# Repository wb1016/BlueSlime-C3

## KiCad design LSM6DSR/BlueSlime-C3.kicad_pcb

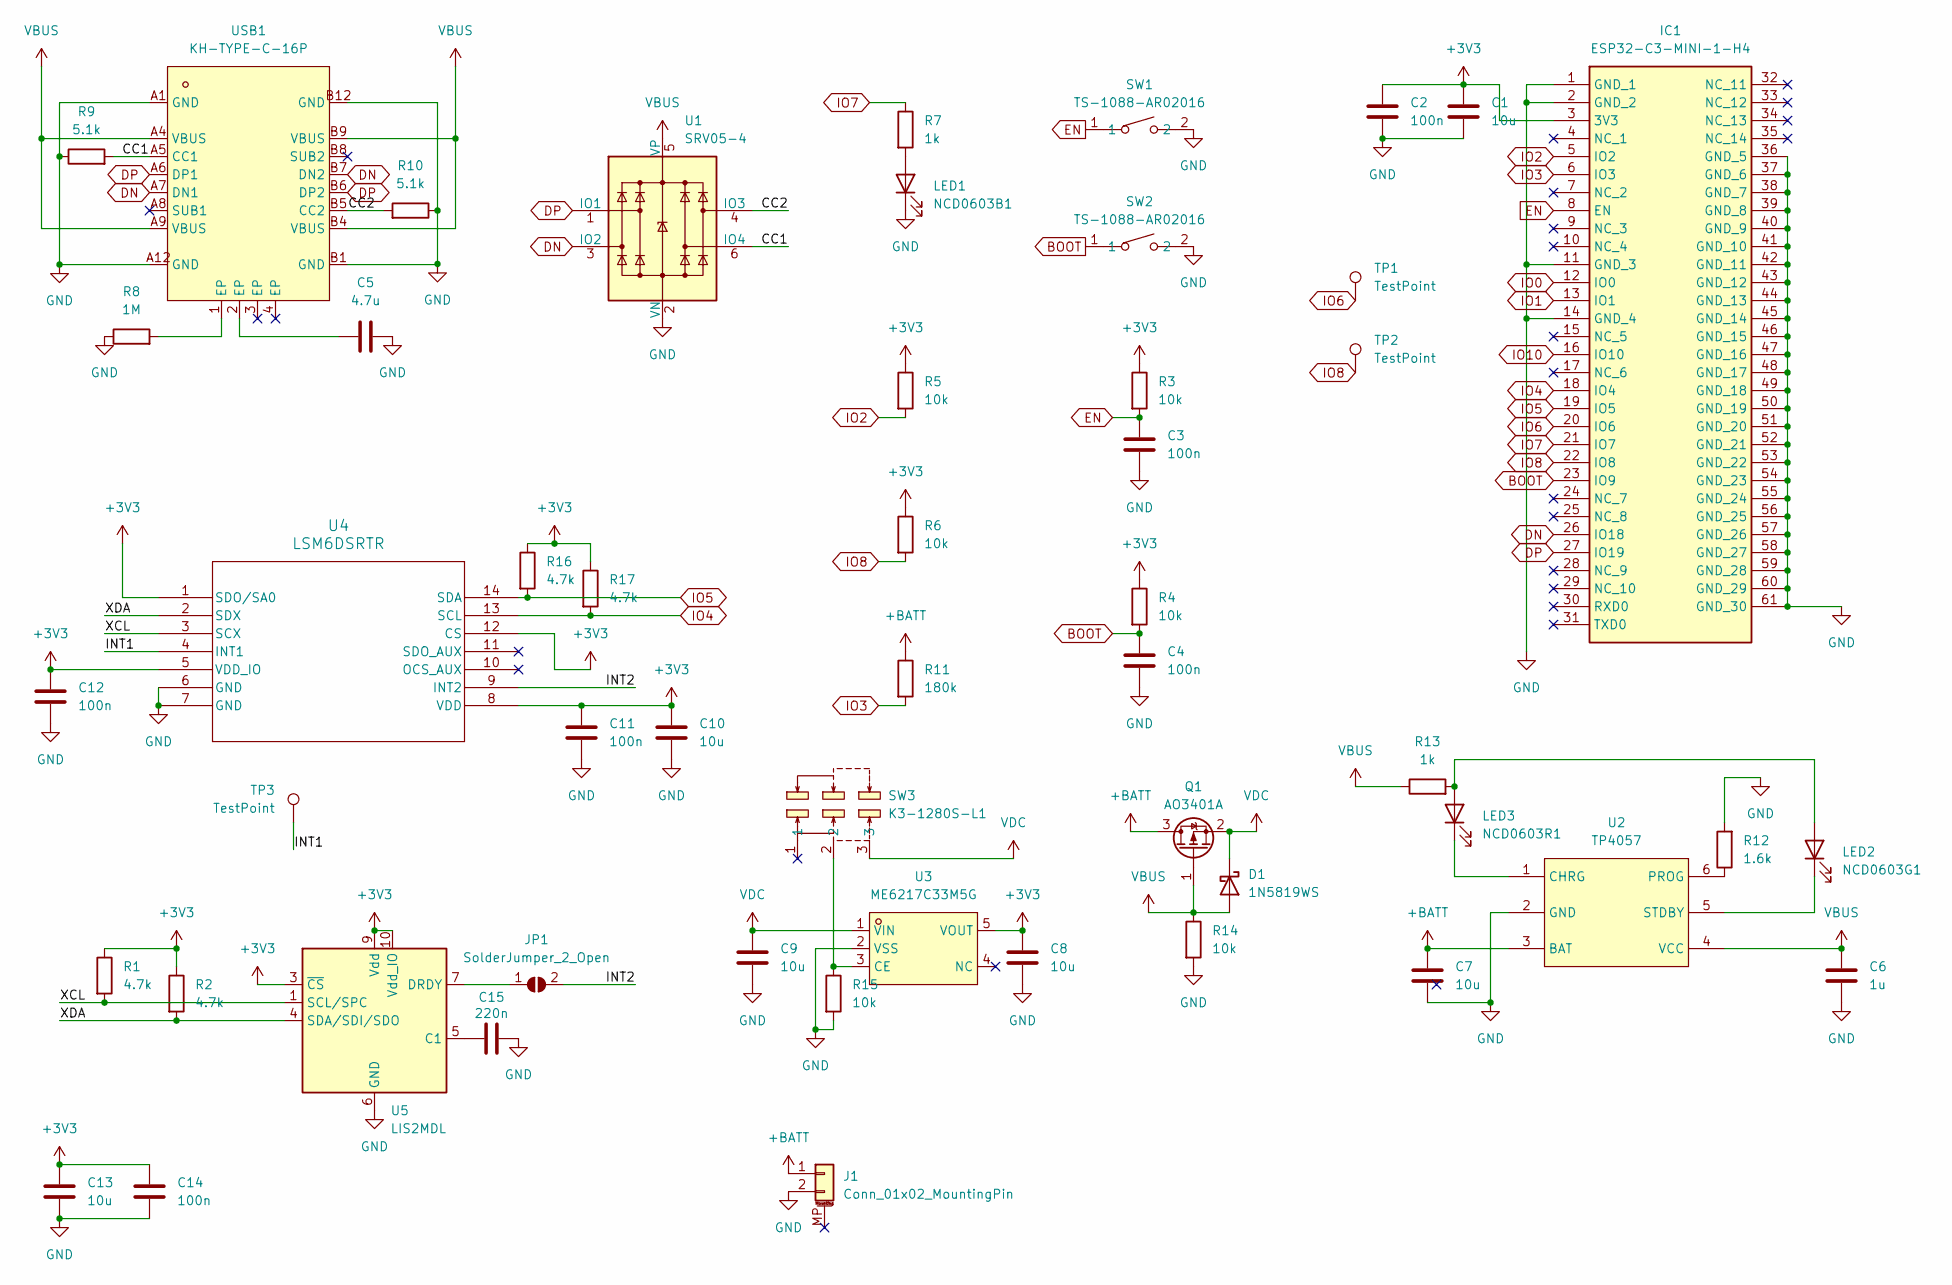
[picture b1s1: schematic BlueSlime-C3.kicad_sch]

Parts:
C1, C7, C8, C9, C10, C13: 10u; C_0603_1608Metric
C2, C3, C4, C11, C12, C14: 100n; C_0402_1005Metric
C5: 4.7u; C_0603_1608Metric
C6: 1u; C_0603_1608Metric
C15: 220n; C_0402_1005Metric
D1: 1N5819WS; D_SOD-323
IC1: ESP32-C3-MINI-1-H4; ESP32C3MINI1H4; Mouser Part Number 356-ESP32-C3-MINI1H4
J1: Conn_01x02_MountingPin; Molex_PicoBlade_53261-0271_1x02-1MP_P1.25mm_Horizontal
JP1: SolderJumper_2_Open; SolderJumper-2_P1.3mm_Open_Pad1.0x1.5mm
LED1: NCD0603B1; LED_0603_1608Metric
LED2: NCD0603G1; LED_0603_1608Metric
LED3: NCD0603R1; LED_0603_1608Metric
Q1: AO3401A; SOT-23
R1, R2, R16, R17: 4.7k; R_0402_1005Metric
R3, R4, R5, R6, R14, R15: 10k; R_0402_1005Metric
R7, R13: 1k; R_0402_1005Metric
R8: 1M; R_0402_1005Metric
R9, R10: 5.1k; R_0402_1005Metric
R11: 180k; R_0402_1005Metric
R12: 1.6k; R_0402_1005Metric
SW1, SW2: TS-1088-AR02016; SW-SMD_L3.9-W3.0-P4.45; LCSC Part C720477
SW3: K3-1280S-L1; SW-SMD_K3-1280S-L1; LCSC Part C223845
TP1, TP2, TP3: TestPoint; TestPoint_Pad_D2.0mm
U1: SRV05-4; SOT-23-6
U2: TP4057; SOT-23-6_L2.9-W1.6-P0.95-LS2.8-BL; LCSC Part C12044
U3: ME6217C33M5G; SOT-23-5_L3.0-W1.7-P0.95-LS2.8-BR; LCSC Part C427602
U4: LSM6DSRTR; LGA-14L_2P5X3X0P83_STM
U5: LIS2MDL; LGA-12_2x2mm_P0.5mm
USB1: KH-TYPE-C-16P; USB-C-SMD_KH-TYPE-C-16P; LCSC Part C709357

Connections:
+3V3: C1.1, C2.1, C8.1, C10.1, C11.1, C12.1, C13.2, C14.1, IC1.3 (3V3), R1.1, R2.1, R3.1, R4.1, R5.1, R6.1, R16.1, R17.1, U3.5 (VOUT), U4.1 (SDO/SA0), U4.5 (VDD_IO), U4.8 (VDD), U4.12 (CS), U5.3 (~CS), U5.9 (Vdd), U5.10 (Vdd_IO)
+BATT: C7.1, J1.1, Q1.3 (D), R11.1, U2.3 (BAT)
/CC1: R9.2, U1.6 (IO4), USB1.A5 (CC1)
/CC2: R10.2, U1.4 (IO3), USB1.B5 (CC2)
/INT1: TP3.1, U4.4 (INT1)
/INT2: JP1.2 (B), U4.9 (INT2)
/XCL: R1.2, U4.3 (SCX), U5.1 (SCL/SPC)
/XDA: R2.2, U4.2 (SDX), U5.4 (SDA/SDI/SDO)
BOOT: C4.1, IC1.23 (IO9), R4.2, SW2.1
DN: IC1.26 (IO18), U1.3 (IO2), USB1.A7 (DN1), USB1.B7 (DN2)
DP: IC1.27 (IO19), U1.1 (IO1), USB1.A6 (DP1), USB1.B6 (DP2)
EN: C3.1, IC1.8 (EN), R3.2, SW1.1
GND: C1.2, C2.2, C3.2, C4.2, C5.2, C6.2, C7.2, C8.2, C9.2, C10.2, C11.2, C12.2, C13.1, C14.2, C15.2, IC1.1 (GND_1), IC1.2 (GND_2), IC1.11 (GND_3), IC1.14 (GND_4), IC1.36 (GND_5), IC1.37 (GND_6), IC1.38 (GND_7), IC1.39 (GND_8), IC1.40 (GND_9), IC1.41 (GND_10), IC1.42 (GND_11), IC1.43 (GND_12), IC1.44 (GND_13), IC1.45 (GND_14), IC1.46 (GND_15), IC1.47 (GND_16), IC1.48 (GND_17), IC1.49 (GND_18), IC1.50 (GND_19), IC1.51 (GND_20), IC1.52 (GND_21), IC1.53 (GND_22), IC1.54 (GND_23), IC1.55 (GND_24), IC1.56 (GND_25), IC1.57 (GND_26), IC1.58 (GND_27), IC1.59 (GND_28), IC1.60 (GND_29), IC1.61 (GND_30), J1.2, LED1.1 (K), R8.1, R9.1, R10.1, R12.2, R14.2, R15.2, SW1.2, SW2.2, U1.2 (VN), U2.2 (GND), U3.2 (VSS), U4.6 (GND), U4.7 (GND), U5.6 (GND), U5.8 (GND), USB1.A1 (GND), USB1.A12 (GND), USB1.B1 (GND), USB1.B12 (GND)
IO0: IC1.12 (IO0)
IO1: IC1.13 (IO1)
IO2: IC1.5 (IO2), R5.2
IO3: IC1.6 (IO3), R11.2
IO4: IC1.18 (IO4), R17.2, U4.13 (SCL)
IO5: IC1.19 (IO5), R16.2, U4.14 (SDA)
IO6: IC1.20 (IO6), TP1.1
IO7: IC1.21 (IO7), R7.1
IO8: IC1.22 (IO8), R6.2, TP2.1
IO10: IC1.16 (IO10)
unnamed: C5.1, USB1.2 (EP)
unnamed: JP1.1 (A), U5.7 (DRDY)
unnamed: LED1.2 (A), R7.2
unnamed: LED2.2 (A), LED3.2 (A), R13.2
unnamed: LED2.1 (K), U2.5 (STDBY)
unnamed: LED3.1 (K), U2.1 (CHRG)
unnamed: R8.2, USB1.1 (EP)
unnamed: R12.1, U2.6 (PROG)
unnamed: R15.1, SW3.2, U3.3 (CE)
unnamed: C15.1, U5.5 (C1)
VBUS: C6.1, D1.2 (A), Q1.1 (G), R13.1, R14.1, U1.5 (VP), U2.4 (VCC), USB1.A4 (VBUS), USB1.A9 (VBUS), USB1.B4 (VBUS), USB1.B9 (VBUS)
VDC: C9.1, D1.1 (K), Q1.2 (S), SW3.3, U3.1 (VIN)

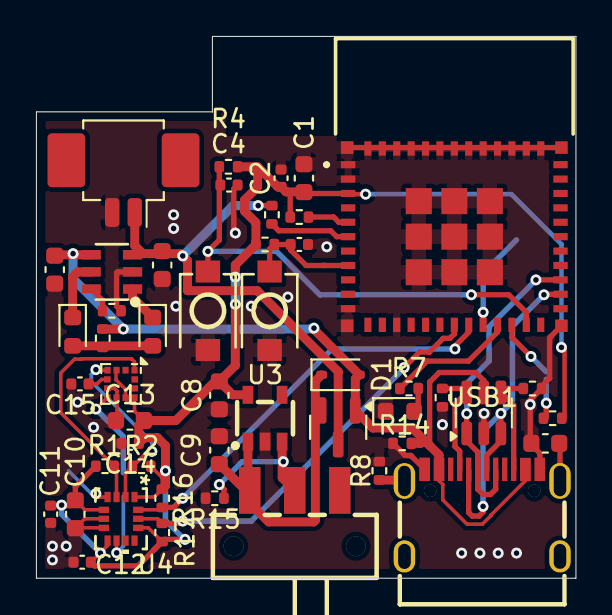
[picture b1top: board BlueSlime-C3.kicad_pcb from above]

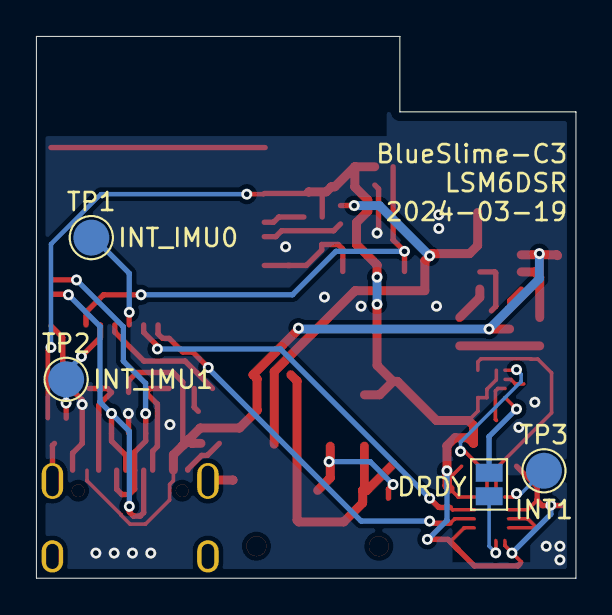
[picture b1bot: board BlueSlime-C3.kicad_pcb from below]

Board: 2 copper layers, 30.0 x 30.1 mm, 52 parts (4 on the bottom side), 32 nets.

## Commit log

2024-05-10 gitignore
